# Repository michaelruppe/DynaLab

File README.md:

DynaLab is a low-cost dynamics lab that allows students to perform System Identification on a real Mass-Spring-Damper system.

*Designed by Michael Ruppe for Monash University with funding from MathWorks®*

## Case
The printed case and acrylic lid were modeled in OnShape. You can inspect and fork your own copy of the [OnShape project](https://cad.onshape.com/documents/9c2f20cdbdc0ad1f01a0b817/w/781d57bc81f27fd7521e8d8c/e/460a2fa13b5ff0fbf298da99?renderMode=0&uiState=6969b017818b6df756886df9)

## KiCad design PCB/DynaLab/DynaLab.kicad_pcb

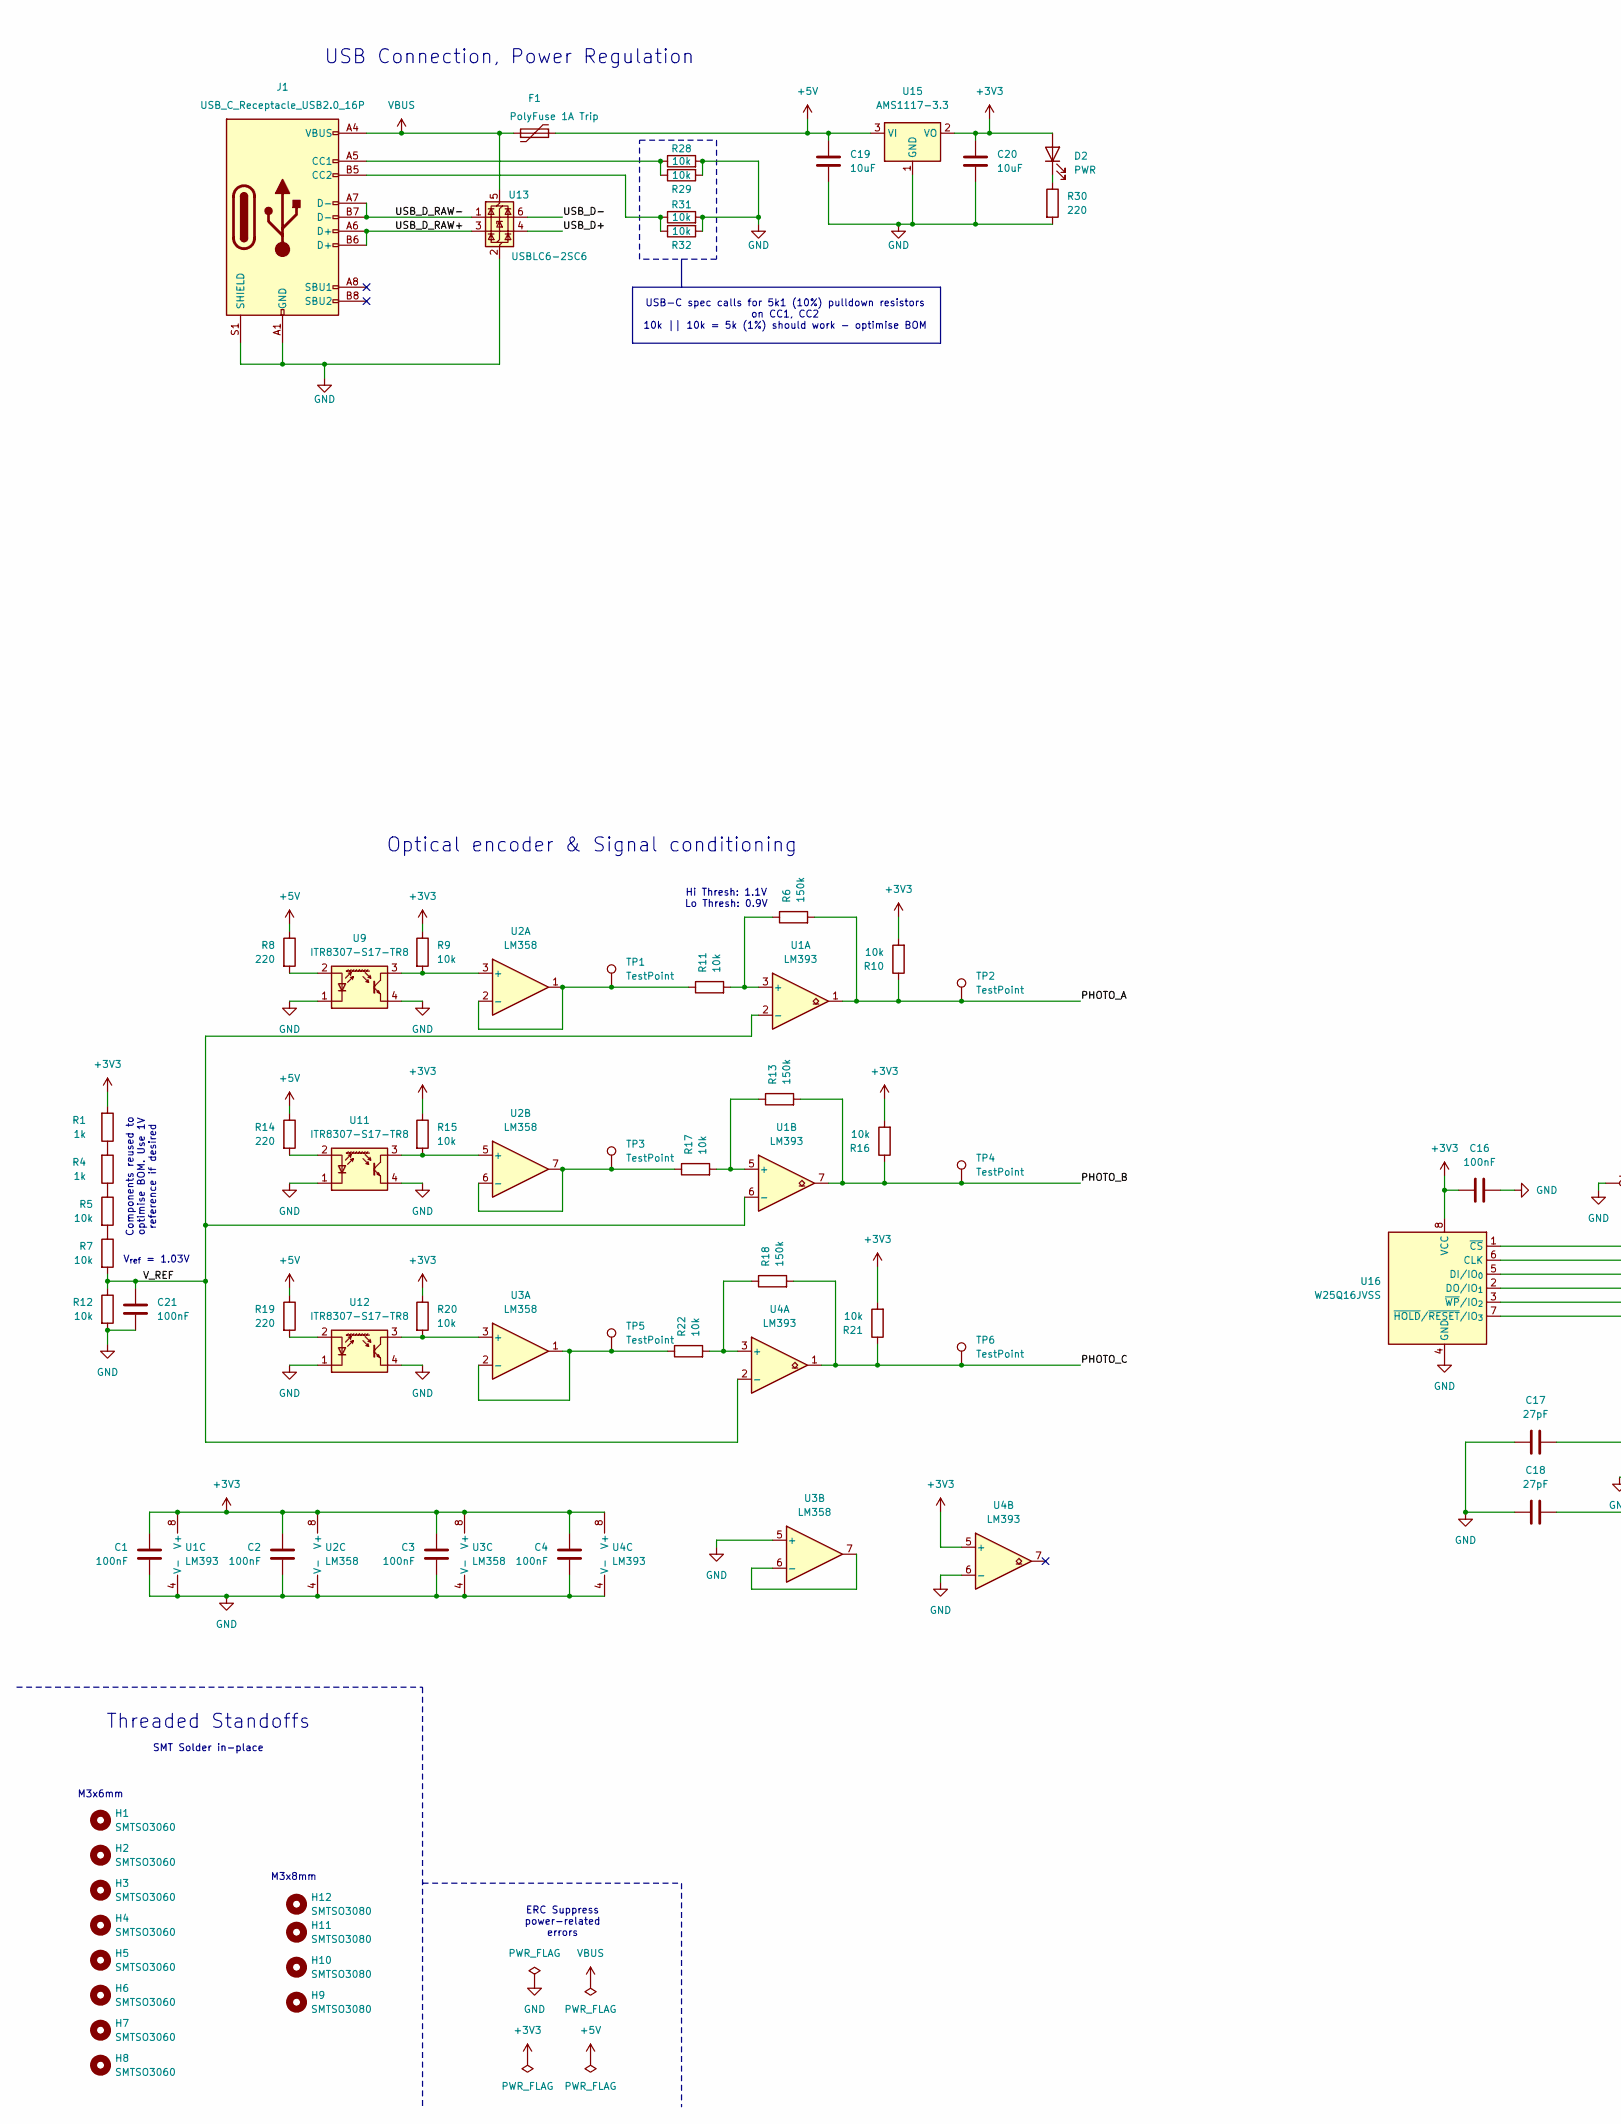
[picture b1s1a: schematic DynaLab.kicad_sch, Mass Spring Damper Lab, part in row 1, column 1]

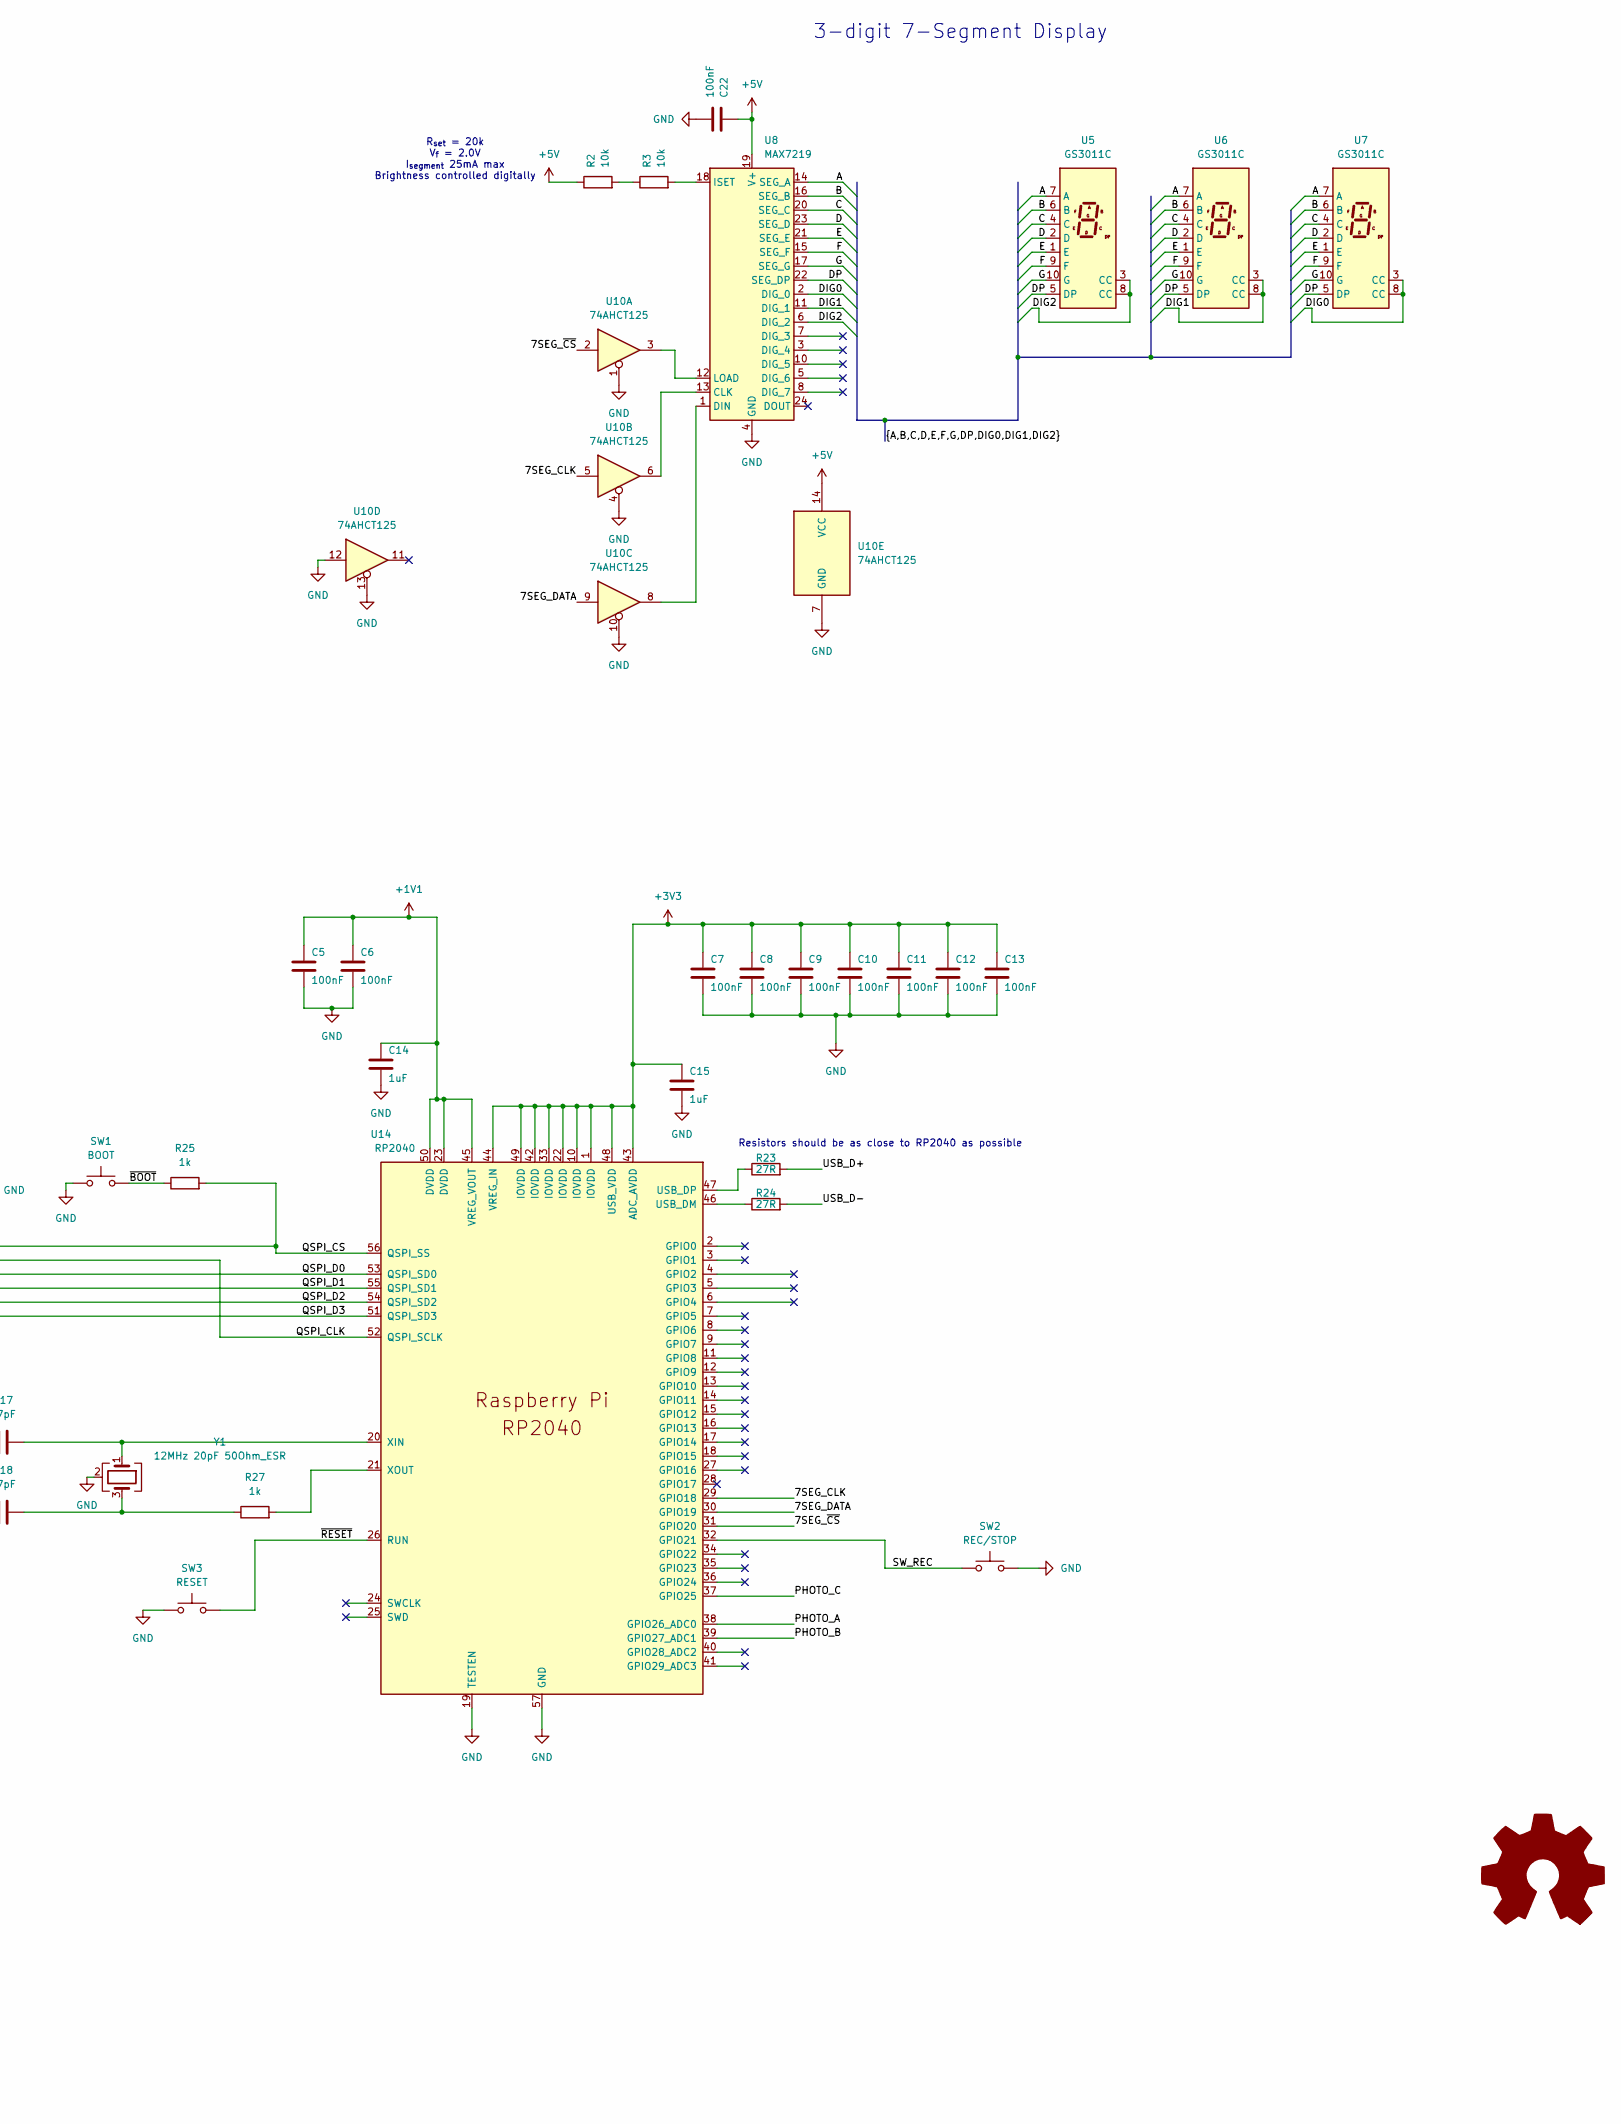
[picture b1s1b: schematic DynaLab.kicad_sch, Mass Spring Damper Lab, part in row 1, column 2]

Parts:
C1, C2, C3, C4, C5, C6, C7, C8, C9, C10, C11, C12, C13, C16, C21, C22: 100nF; C_0603_1608Metric; LCSC Part # C14663
C14, C15: 1uF; C_0603_1608Metric; LCSC Part # C15849
C17, C18: 27pF; C_0603_1608Metric; LCSC Part # C1656
C19, C20: 10uF; C_0603_1608Metric; LCSC Part # C19702
D2: PWR; LED_0603_1608Metric; LCSC Part # C965807
F1: PolyFuse 1A Trip; R_1206_3216Metric; LCSC Part # C720075
H1, H2, H3, H4, H5, H6, H7, H8: SMTSO3060; MountingHole_SMTSO3060_3.2mm_M3; LCSC Part # C2915637
H9, H10, H11, H12: SMTSO3080; MountingHole_SMTSO3080_3.2mm_M3; LCSC Part # C2916369
J1: USB_C_Receptacle_USB2.0_16P; USB_C_Receptacle_HCTL_HC-TYPE-C-16P-01A; LCSC Part # C2894897
R1, R4, R25, R27: 1k; R_0603_1608Metric; LCSC Part # C21190
R2, R3, R5, R7, R9, R10, R11, R12, R15, R16, R17, R20, R21, R22, R28, R29, R31, R32: 10k; R_0603_1608Metric; LCSC Part # C25804
R6, R13, R18: 150k; R_0603_1608Metric; LCSC Part # C22807
R8, R14, R19, R30: 220; R_0603_1608Metric; LCSC Part # C22962
R23, R24: 27R; R_0603_1608Metric; LCSC Part # C25190
SW1: BOOT; SW_Push_1P1T_NO_E-Switch_TL3301NxxxxxG; LCSC Part # C455109
SW2: REC/STOP; SW_SPST_Omron_B3F-40xx; LCSC Part # C84931
SW3: RESET; SW_SPST_Omron_B3F-40xx; LCSC Part # C84931
TP1, TP2, TP3, TP4, TP5, TP6: TestPoint; TestPoint_Pad_D1.5mm
U1, U4: LM393; SOIC-8_3.9x4.9mm_P1.27mm; LCSC Part # C32901
U2, U3: LM358; SOIC-8_3.9x4.9mm_P1.27mm; LCSC Part # C9418
U5, U6, U7: GS3011C; GS3011A; LCSC Part # C22462660
U8: MAX7219; SOIC-24W_7.5x15.4mm_P1.27mm; LCSC Part # C49443603
U9, U11, U12: ITR8307-S17-TR8; Everlight_ITR1201SR10AR; LCSC Part # C81632
U10: 74AHCT125; SOIC-14_3.9x8.7mm_P1.27mm; LCSC Part # C5962
U13: USBLC6-2SC6; SOT-23-6; LCSC Part # C2687116
U14: RP2040; RP2040-QFN-56; PARTREV 1.6.1; LCSC Part # C2040
U15: AMS1117-3.3; SOT-223-3_TabPin2; LCSC Part # C6186
U16: W25Q16JVSS; SOIC-8_5.3x5.3mm_P1.27mm; LCSC Part # C82317
Y1: 12MHz 20pF 50Ohm_ESR; Crystal_SMD_3225-4Pin_3.2x2.5mm; LCSC Part # C133334

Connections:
+1V1: C5.1, C6.1, C14.1, U14.23 (DVDD), U14.45 (VREG_VOUT), U14.50 (DVDD)
+3V3: C1.1, C2.1, C3.1, C4.1, C7.1, C8.1, C9.1, C10.1, C11.1, C12.1, C13.1, C15.1, C16.1, C20.1, D2.2 (A), R1.2, R9.1, R10.2, R15.1, R16.2, R20.1, R21.2, U1.8 (V+), U2.8 (V+), U3.8 (V+), U4.5 (+), U4.8 (V+), U14.1 (IOVDD), U14.10 (IOVDD), U14.22 (IOVDD), U14.33 (IOVDD), U14.42 (IOVDD), U14.43 (ADC_AVDD), U14.44 (VREG_IN), U14.48 (USB_VDD), U14.49 (IOVDD), U15.2 (VO), U16.8 (VCC)
+5V: C19.1, C22.1, F1.2, R2.1, R8.1, R14.1, R19.1, U8.19 (V+), U10.14 (VCC), U15.3 (VI)
/7SEG_CLK: U10.5, U14.29 (GPIO18)
/7SEG_DATA: U10.9, U14.30 (GPIO19)
/7SEG_~CS: U10.2, U14.31 (GPIO20)
/A: U5.7 (A), U6.7 (A), U7.7 (A), U8.14 (SEG_A)
/B: U5.6 (B), U6.6 (B), U7.6 (B), U8.16 (SEG_B)
/C: U5.4 (C), U6.4 (C), U7.4 (C), U8.20 (SEG_C)
/D: U5.2 (D), U6.2 (D), U7.2 (D), U8.23 (SEG_D)
/DIG0: U7.3 (CC), U7.8 (CC), U8.2 (DIG_0)
/DIG1: U6.3 (CC), U6.8 (CC), U8.11 (DIG_1)
/DIG2: U5.3 (CC), U5.8 (CC), U8.6 (DIG_2)
/DP: U5.5 (DP), U6.5 (DP), U7.5 (DP), U8.22 (SEG_DP)
/E: U5.1 (E), U6.1 (E), U7.1 (E), U8.21 (SEG_E)
/F: U5.9 (F), U6.9 (F), U7.9 (F), U8.15 (SEG_F)
/G: U5.10 (G), U6.10 (G), U7.10 (G), U8.17 (SEG_G)
/PHOTO_A: R6.2, R10.1, TP2.1, U1.1, U14.38 (GPIO26_ADC0)
/PHOTO_B: R13.2, R16.1, TP4.1, U1.7, U14.39 (GPIO27_ADC1)
/PHOTO_C: R18.2, R21.1, TP6.1, U4.1, U14.37 (GPIO25)
/QSPI_CLK: U14.52 (QSPI_SCLK), U16.6 (CLK)
/QSPI_CS: R25.2, U14.56 (QSPI_SS), U16.1 (~CS)
/QSPI_D0: U14.53 (QSPI_SD0), U16.5 (DI/IO_{0})
/QSPI_D1: U14.55 (QSPI_SD1), U16.2 (DO/IO_{1})
/QSPI_D2: U14.54 (QSPI_SD2), U16.3 (~WP/IO_{2})
/QSPI_D3: U14.51 (QSPI_SD3), U16.7 (~HOLD/~RESET/IO_{3})
/SW_REC: SW2.1, U14.32 (GPIO21)
/USB_D+: R23.2, U13.4 (I/O2)
/USB_D-: R24.2, U13.6 (I/O1)
/USB_D_RAW+: J1.A6 (D+), J1.B6 (D+), U13.3 (I/O2)
/USB_D_RAW-: J1.A7 (D-), J1.B7 (D-), U13.1 (I/O1)
/V_REF: C21.1, R7.2, R12.1, U1.2 (-), U1.6 (-), U4.2 (-)
/~BOOT: R25.1, SW1.1
/~RESET: SW3.1, U14.26 (RUN)
GND: C1.2, C2.2, C3.2, C4.2, C5.2, C6.2, C7.2, C8.2, C9.2, C10.2, C11.2, C12.2, C13.2, C14.2, C15.2, C16.2, C17.1, C18.1, C19.2, C20.2, C21.2, C22.2, J1.A1 (GND), J1.A12 (GND), J1.B1 (GND), J1.B12 (GND), J1.S1 (SHIELD), R12.2, R28.2, R29.2, R30.2, R31.2, R32.2, SW1.2, SW2.2, SW3.2, U1.4 (V-), U2.4 (V-), U3.4 (V-), U3.5 (+), U4.4 (V-), U4.6 (-), U8.4 (GND), U8.9 (GND), U9.1 (K), U9.4, U10.1, U10.4, U10.7 (GND), U10.10, U10.12, U10.13, U11.1 (K), U11.4, U12.1 (K), U12.4, U13.2 (GND), U14.19 (TESTEN), U14.57 (GND), U15.1 (GND), U16.4 (GND), Y1.2 (G), Y1.4 (G)
unnamed: C18.2, R27.1, Y1.3
unnamed: D2.1 (K), R30.1
unnamed: J1.A5 (CC1), R28.1, R29.1
unnamed: J1.B5 (CC2), R31.1, R32.1
unnamed: R1.1, R4.2
unnamed: R2.2, R3.1
unnamed: R4.1, R5.1
unnamed: R5.2, R7.1
unnamed: R6.1, R11.2, U1.3 (+)
unnamed: R13.1, R17.2, U1.5 (+)
unnamed: R9.2, U2.3 (+), U9.3
unnamed: R11.1, TP1.1, U2.1, U2.2 (-)
unnamed: R15.2, U2.5 (+), U11.3
unnamed: R17.1, TP3.1, U2.6 (-), U2.7
unnamed: R20.2, U3.3 (+), U12.3
unnamed: R22.1, TP5.1, U3.1, U3.2 (-)
unnamed: U3.6 (-), U3.7
unnamed: R18.1, R22.2, U4.3 (+)
unnamed: U8.13 (CLK), U10.6
unnamed: U8.1 (DIN), U10.8
unnamed: R3.2, U8.18 (ISET)
unnamed: U8.12 (LOAD), U10.3
unnamed: R8.2, U9.2 (A)
unnamed: R14.2, U11.2 (A)
unnamed: R19.2, U12.2 (A)
unnamed: R24.1, U14.46 (USB_DM)
unnamed: R23.1, U14.47 (USB_DP)
unnamed: C17.2, U14.20 (XIN), Y1.1
unnamed: R27.2, U14.21 (XOUT)
VBUS: F1.1, J1.A4 (VBUS), J1.A9 (VBUS), J1.B4 (VBUS), J1.B9 (VBUS), U13.5 (VBUS)

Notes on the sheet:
USB-C spec calls for 5k1 (10%) pulldown resistors on CC1, CC2 10k || 10k = 5k (1%) should work - optimise BOM
M3x6mm
Resistors should be as close to RP2040 as possible
Hi Thresh: 1.1V Lo Thresh: 0.9V
3-digit 7-Segment Display
Threaded Standoffs
Components reused to optimise BOM. Use 1V reference if desired
USB Connection, Power Regulation
ERC Suppress power-related errors
SMT Solder in-place
R_{set} = 20k V_{f} = 2.0V I_{segment} 25mA max Brightness controlled digitally
Optical encoder & Signal conditioning
M3x8mm
V_{ref} = 1.03V

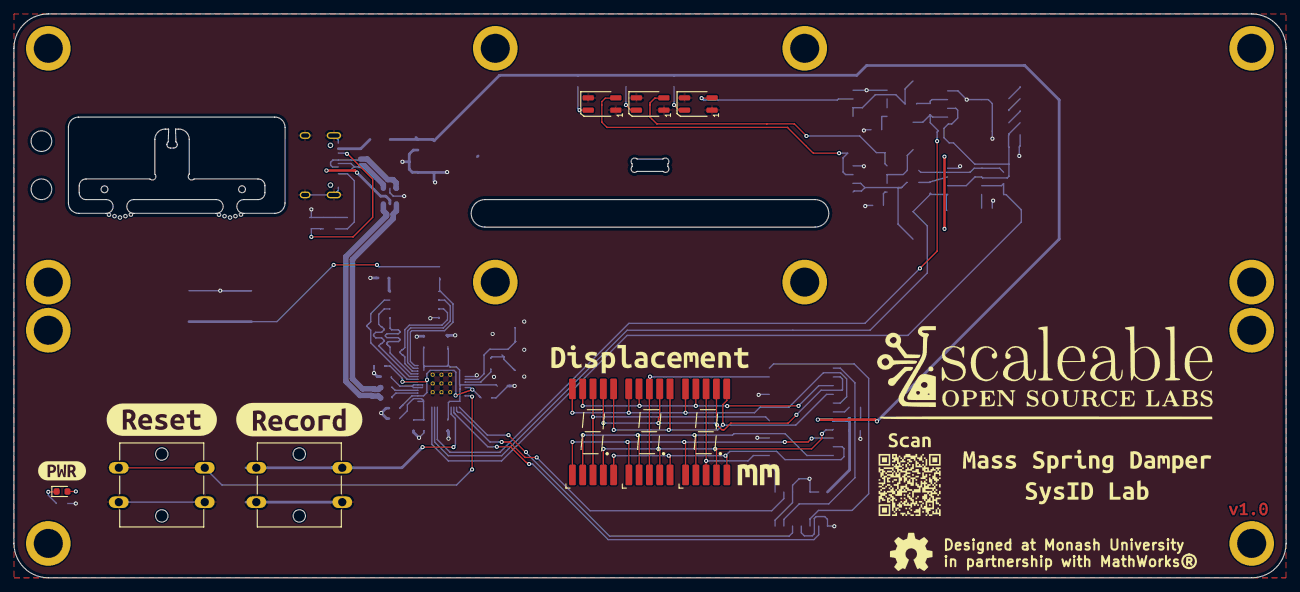
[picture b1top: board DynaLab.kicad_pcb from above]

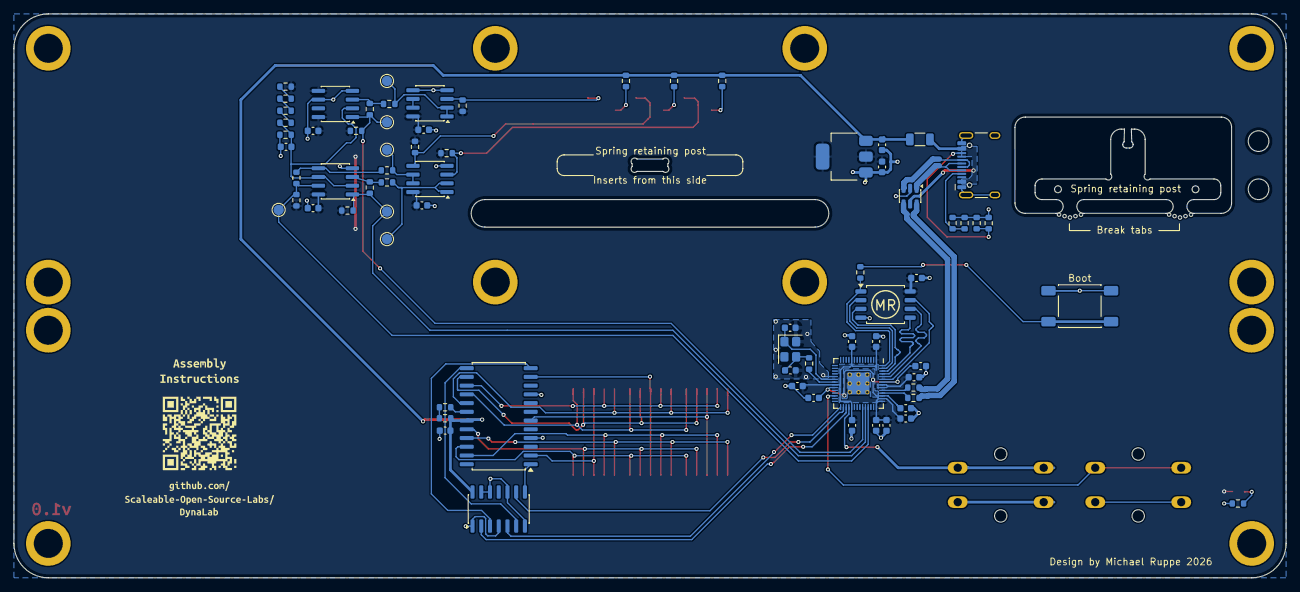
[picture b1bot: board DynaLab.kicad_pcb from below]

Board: 2 copper layers, 185.0 x 82.0 mm, 110 parts (86 on the bottom side), 65 nets.

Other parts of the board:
kibuzzard-6930AF86: G***; kibuzzard-6930AF86
kibuzzard-6930AFAB: G***; kibuzzard-6930AFAB
kibuzzard-69645CED: G***; kibuzzard-69645CED
kibuzzard-697836DA: G***; kibuzzard-697836DA
kibuzzard-697848C9: G***; kibuzzard-697848C9
kibuzzard-6964435B: G***; kibuzzard-6964435B
kibuzzard-6978203B: G***; kibuzzard-6978203B
kibuzzard-6978204E: G***; kibuzzard-6978204E
kibuzzard-6978363D: G***; kibuzzard-6978363D
kibuzzard-6978422B: G***; kibuzzard-6978422B
kibuzzard-69310180: G***; kibuzzard-69310180
kibuzzard-69310240: G***; kibuzzard-69310240
kibuzzard-69783696: G***; kibuzzard-69783696
kibuzzard-69784254: G***; kibuzzard-69784254
mousebite1, mousebite2: VAL**; mouse-bite-2mm-4mm-single-sided

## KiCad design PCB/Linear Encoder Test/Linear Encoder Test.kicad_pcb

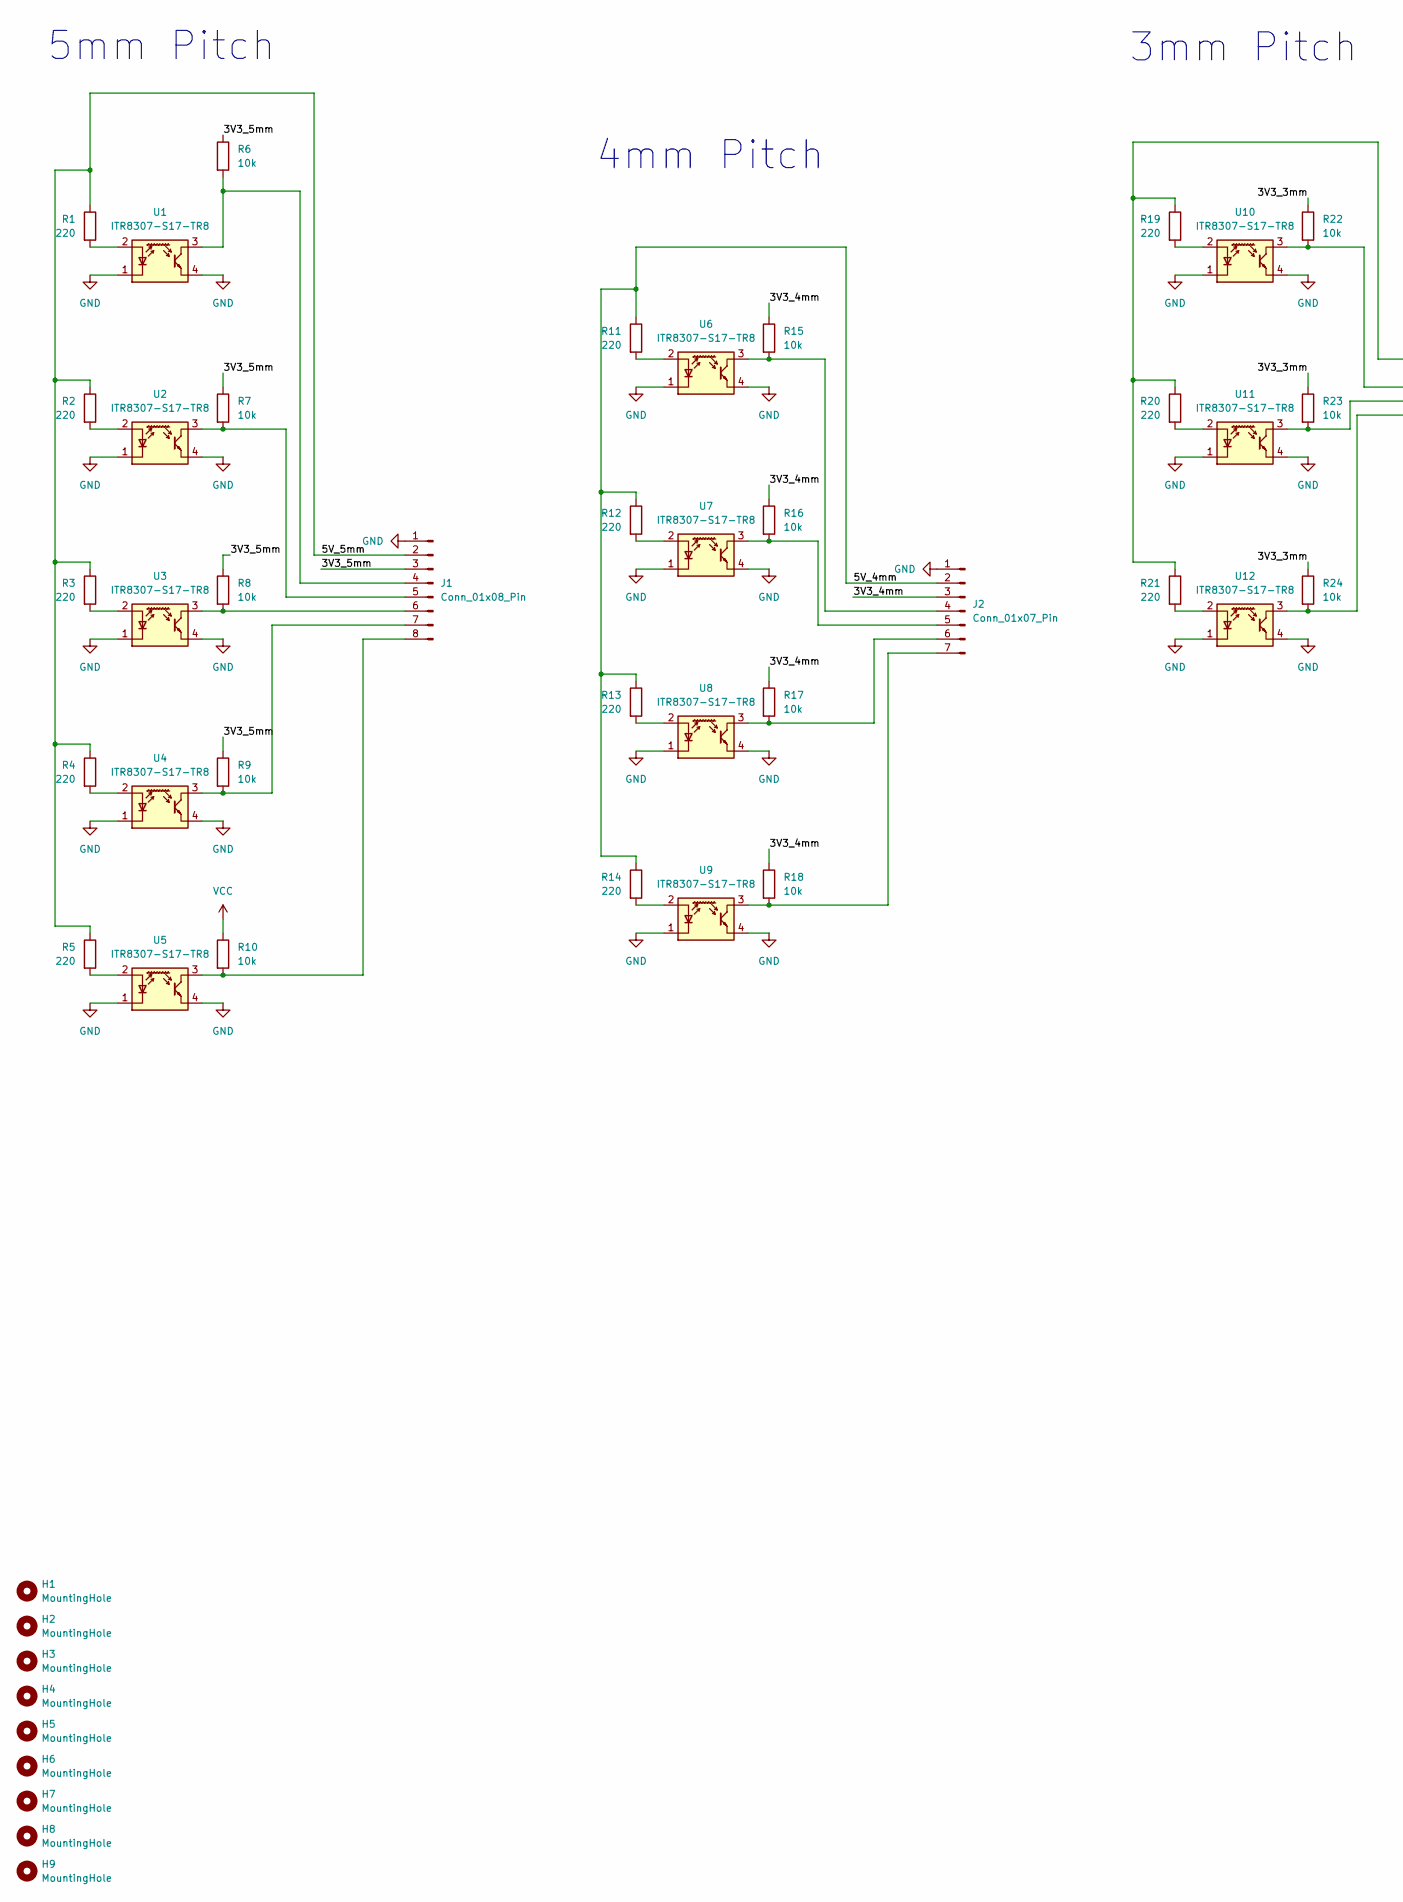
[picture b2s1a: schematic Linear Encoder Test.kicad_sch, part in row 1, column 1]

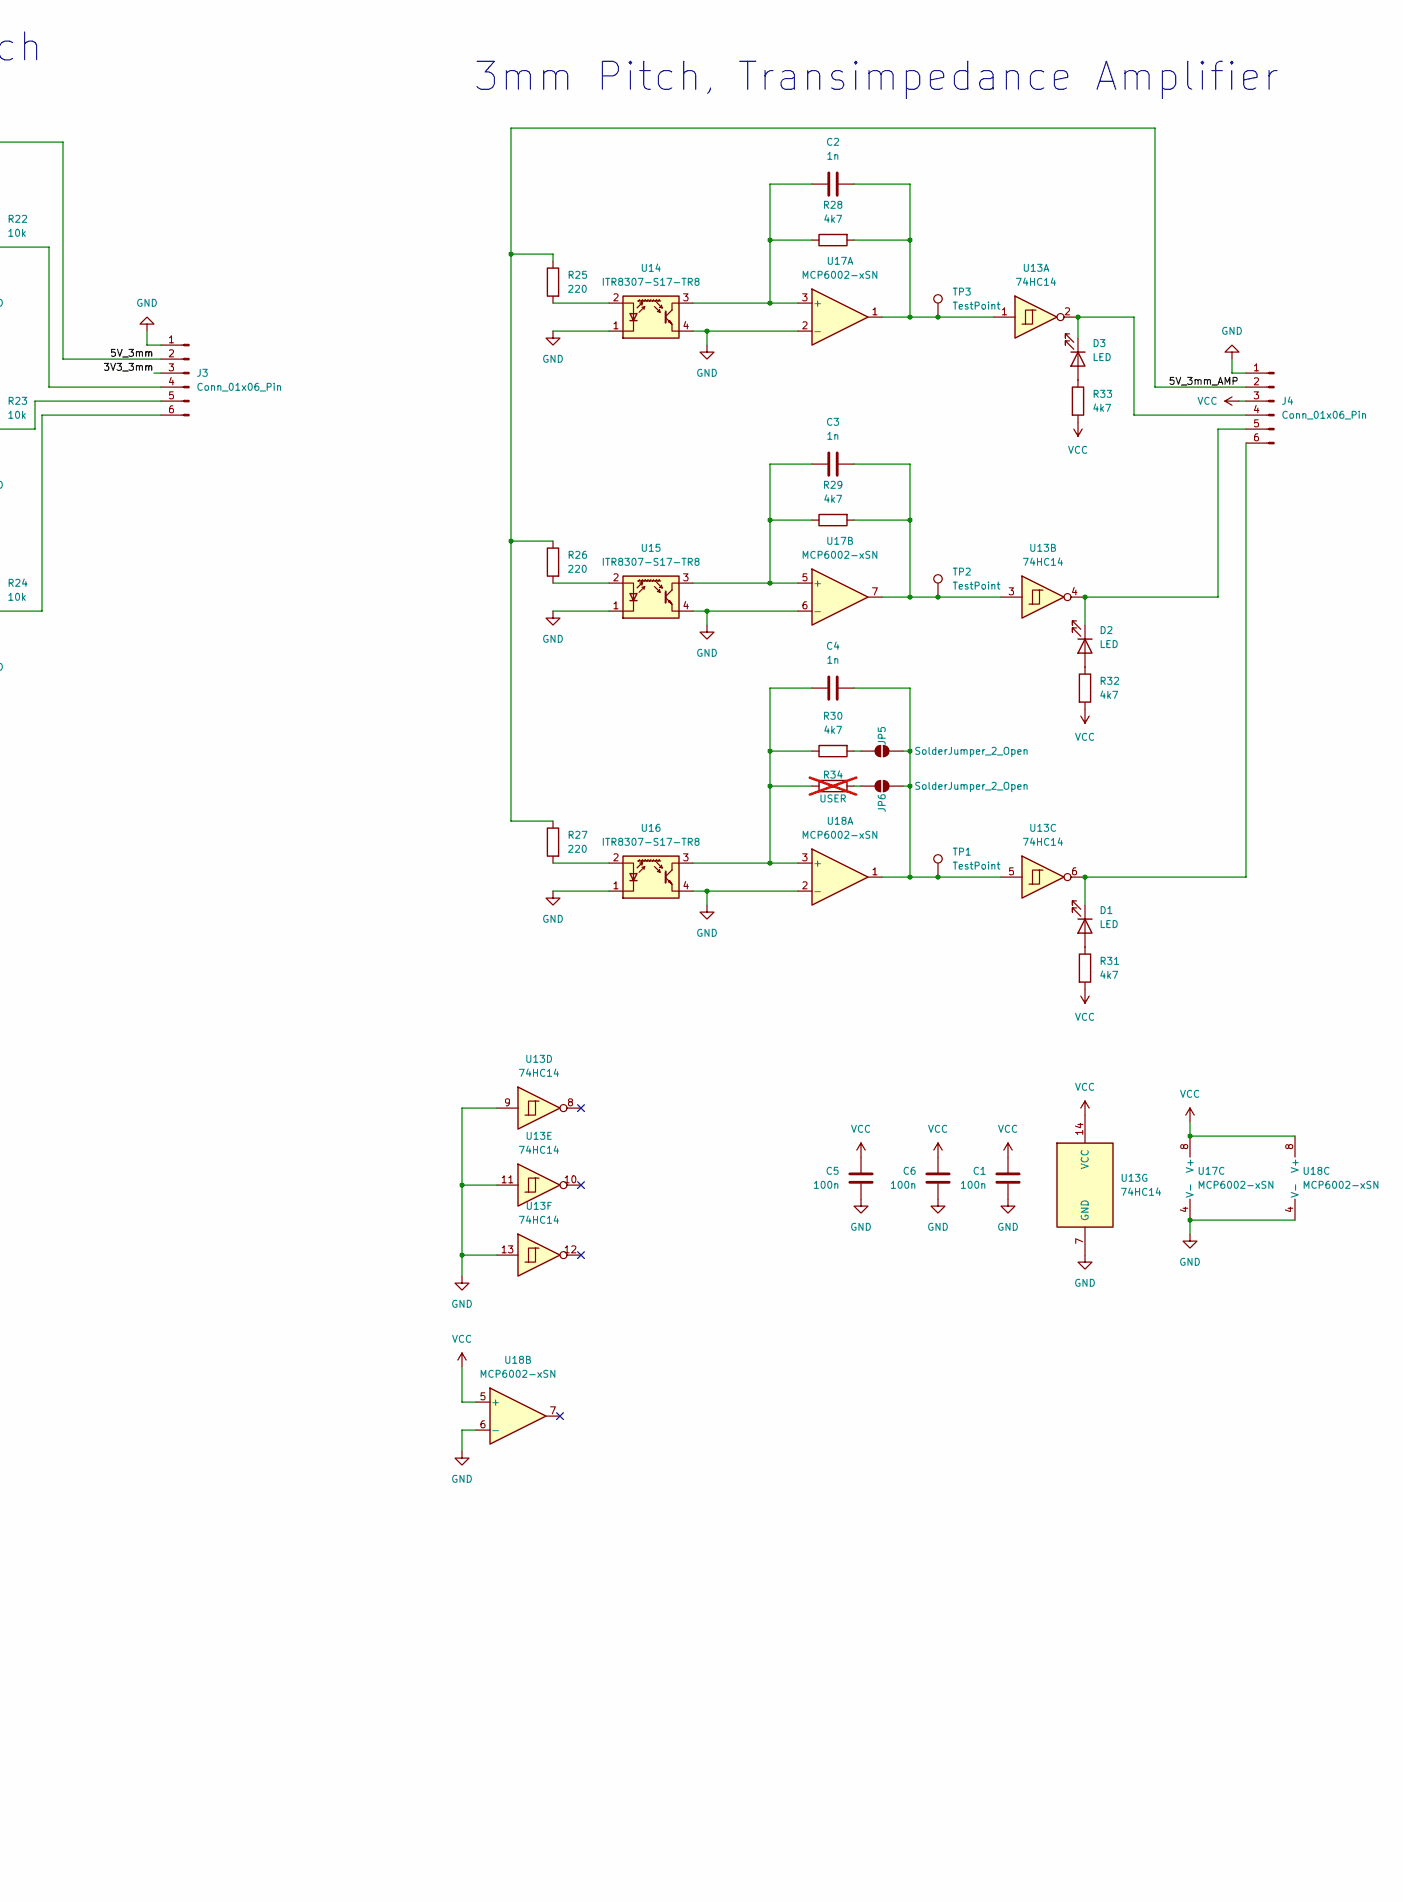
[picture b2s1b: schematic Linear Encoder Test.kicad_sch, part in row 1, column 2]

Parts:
C1, C5, C6: 100n; C_0603_1608Metric
C2, C3, C4: 1n; C_0603_1608Metric
D1, D2, D3: LED; LED_0603_1608Metric
H1, H2, H3, H4, H5, H6, H7, H8, H9: MountingHole; MountingHole_SMTSO3030_3.2mm_M3; LCSC Part # C2915308
J1: Conn_01x08_Pin; PinHeader_1x08_P2.54mm_Vertical
J2: Conn_01x07_Pin; PinHeader_1x07_P2.54mm_Vertical
J3, J4: Conn_01x06_Pin; PinHeader_1x06_P2.54mm_Vertical
JP5, JP6: SolderJumper_2_Open; SolderJumper-2_P1.3mm_Open_RoundedPad1.0x1.5mm
R1, R2, R3, R4, R5, R11, R12, R13, R14, R19, R20, R21, R25, R26, R27: 220; R_0603_1608Metric
R6, R7, R8, R9, R10, R15, R16, R17, R18, R22, R23, R24: 10k; R_0603_1608Metric
R28, R29, R30, R31, R32, R33: 4k7; R_0603_1608Metric
R34: USER; R_0603_1608Metric; not fitted
TP1, TP2, TP3: TestPoint; TestPoint_THTPad_2.0x2.0mm_Drill1.0mm
U1, U2, U3, U4, U5, U6, U7, U8, U9, U10, U11, U12, U14, U15, U16: ITR8307-S17-TR8; Everlight_ITR1201SR10AR; LCSC Part # C81632
U13: 74HC14; SOIC-14_3.9x8.7mm_P1.27mm; LCSC Part # C5605
U17, U18: MCP6002-xSN; SOIC-8_3.9x4.9mm_P1.27mm; LCSC Part # C5145244

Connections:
/3V3_3mm: J3.3, R22.1, R23.1, R24.1
/3V3_4mm: J2.3, R15.1, R16.1, R17.1, R18.1
/3V3_5mm: J1.3, R6.1, R7.1, R8.1, R9.1
/5V_3mm: J3.2, R19.1, R20.1, R21.1
/5V_3mm_AMP: J4.2, R25.1, R26.1, R27.1
/5V_4mm: J2.2, R11.1, R12.1, R13.1, R14.1
/5V_5mm: J1.2, R1.1, R2.1, R3.1, R4.1, R5.1
GND: C1.1, C5.1, C6.1, J1.1, J2.1, J3.1, J4.1, U1.1 (K), U1.4, U2.1 (K), U2.4, U3.1 (K), U3.4, U4.1 (K), U4.4, U5.1 (K), U5.4, U6.1 (K), U6.4, U7.1 (K), U7.4, U8.1 (K), U8.4, U9.1 (K), U9.4, U10.1 (K), U10.4, U11.1 (K), U11.4, U12.1 (K), U12.4, U13.7 (GND), U13.9, U13.11, U13.13, U14.1 (K), U14.4, U15.1 (K), U15.4, U16.1 (K), U16.4, U17.2 (-), U17.4 (V-), U17.6 (-), U18.2 (-), U18.4 (V-), U18.6 (-)
unnamed: C2.2, R28.2, TP3.1, U13.1, U17.1
unnamed: C3.2, R29.2, TP2.1, U13.3, U17.7
unnamed: D1.2 (A), R31.1
unnamed: D1.1 (K), J4.6, U13.6
unnamed: D2.2 (A), R32.1
unnamed: D2.1 (K), J4.5, U13.4
unnamed: D3.2 (A), R33.1
unnamed: D3.1 (K), J4.4, U13.2
unnamed: J1.4, R6.2, U1.3
unnamed: J1.5, R7.2, U2.3
unnamed: J1.6, R8.2, U3.3
unnamed: J1.7, R9.2, U4.3
unnamed: J1.8, R10.2, U5.3
unnamed: J2.4, R15.2, U6.3
unnamed: J2.5, R16.2, U7.3
unnamed: J2.6, R17.2, U8.3
unnamed: J2.7, R18.2, U9.3
unnamed: J3.4, R22.2, U10.3
unnamed: J3.5, R23.2, U11.3
unnamed: J3.6, R24.2, U12.3
unnamed: JP5.1 (A), R30.2
unnamed: C4.2, JP5.2 (B), JP6.2 (B), TP1.1, U13.5, U18.1
unnamed: JP6.1 (A), R34.2
unnamed: R1.2, U1.2 (A)
unnamed: R2.2, U2.2 (A)
unnamed: R3.2, U3.2 (A)
unnamed: R4.2, U4.2 (A)
unnamed: R5.2, U5.2 (A)
unnamed: R11.2, U6.2 (A)
unnamed: R12.2, U7.2 (A)
unnamed: R13.2, U8.2 (A)
unnamed: R14.2, U9.2 (A)
unnamed: R19.2, U10.2 (A)
unnamed: R20.2, U11.2 (A)
unnamed: R21.2, U12.2 (A)
unnamed: R25.2, U14.2 (A)
unnamed: R26.2, U15.2 (A)
unnamed: R27.2, U16.2 (A)
unnamed: C2.1, R28.1, U14.3, U17.3 (+)
unnamed: C3.1, R29.1, U15.3, U17.5 (+)
unnamed: C4.1, R30.1, R34.1, U16.3, U18.3 (+)
VCC: C1.2, C5.2, C6.2, J4.3, R10.1, R31.2, R32.2, R33.2, U13.14 (VCC), U17.8 (V+), U18.5 (+), U18.8 (V+)

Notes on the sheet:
3mm Pitch
3mm Pitch, Transimpedance Amplifier
4mm Pitch
5mm Pitch

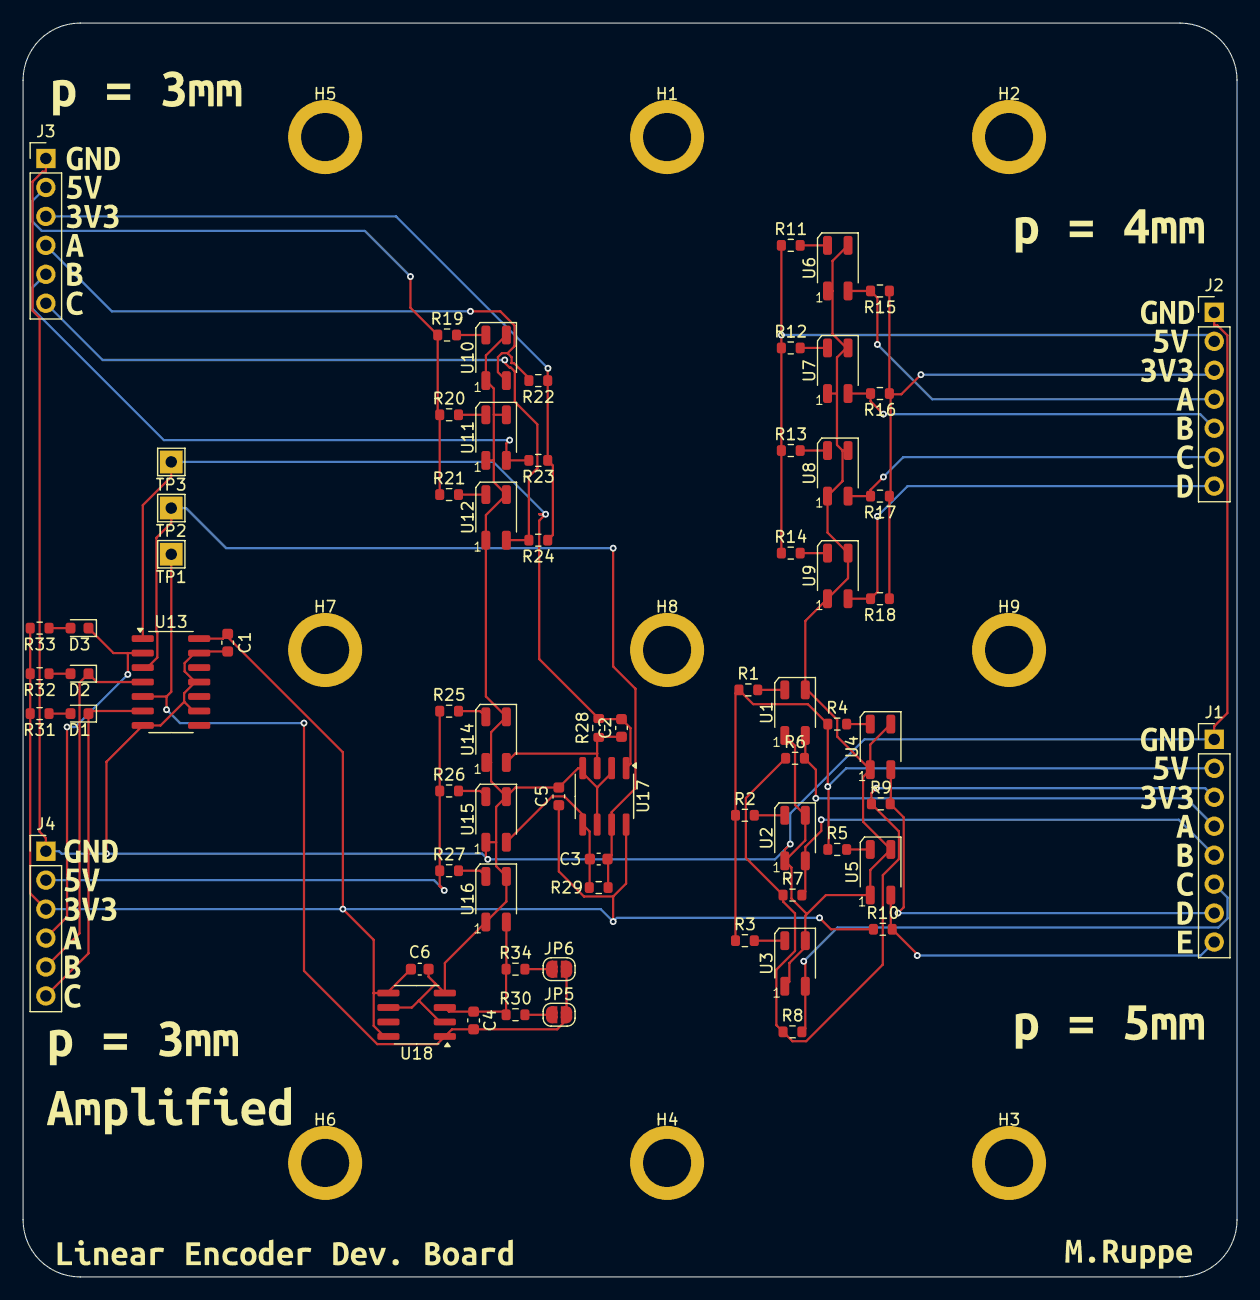
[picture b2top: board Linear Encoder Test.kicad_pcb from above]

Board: 2 copper layers, 106.5 x 110.0 mm, 112 parts (0 on the bottom side), 50 nets.

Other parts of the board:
kibuzzard-68A3D4DA, kibuzzard-68A3D4DA#2, kibuzzard-68A3D4DA#3, kibuzzard-68A3D4DA#4: G***; kibuzzard-68A3D4DA
kibuzzard-68A3D4E7, kibuzzard-68A3D4E7#2, kibuzzard-68A3D4E7#3, kibuzzard-68A3D4E7#4: G***; kibuzzard-68A3D4E7
kibuzzard-68A3D4F1, kibuzzard-68A3D4F1#2, kibuzzard-68A3D4F1#3, kibuzzard-68A3D4F1#4: G***; kibuzzard-68A3D4F1
kibuzzard-68A3D6CA, kibuzzard-68A3D6CA#2: G***; kibuzzard-68A3D6CA
kibuzzard-68A3D6EB: G***; kibuzzard-68A3D6EB
kibuzzard-68A3D52F, kibuzzard-68A3D52F#2, kibuzzard-68A3D52F#3, kibuzzard-68A3D52F#4: G***; kibuzzard-68A3D52F
kibuzzard-68A3D523, kibuzzard-68A3D523#2, kibuzzard-68A3D523#3, kibuzzard-68A3D523#4: G***; kibuzzard-68A3D523
kibuzzard-68A3D529, kibuzzard-68A3D529#2, kibuzzard-68A3D529#3, kibuzzard-68A3D529#4: G***; kibuzzard-68A3D529
kibuzzard-68A3D602: G***; kibuzzard-68A3D602
kibuzzard-68A3D619: G***; kibuzzard-68A3D619
kibuzzard-68A3D628: G***; kibuzzard-68A3D628
kibuzzard-68A3D638: G***; kibuzzard-68A3D638
kibuzzard-68A3D861: G***; kibuzzard-68A3D861
kibuzzard-68A3DEDD: G***; kibuzzard-68A3DEDD

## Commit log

2025-12-04 ignore auto generated production files
2025-12-04 Add README.md
2025-12-16 basic functionality for DynaLab prototype
2026-01-08 compatible with windows, dirty code
2026-01-11 change readme to .htm, randomise data file name slug
2026-01-21 ignore log files
2026-01-21 atomise PCB projects for portability
2026-01-21 add purchasing #s and some datasheets
2026-01-29 repo and library maintenance
